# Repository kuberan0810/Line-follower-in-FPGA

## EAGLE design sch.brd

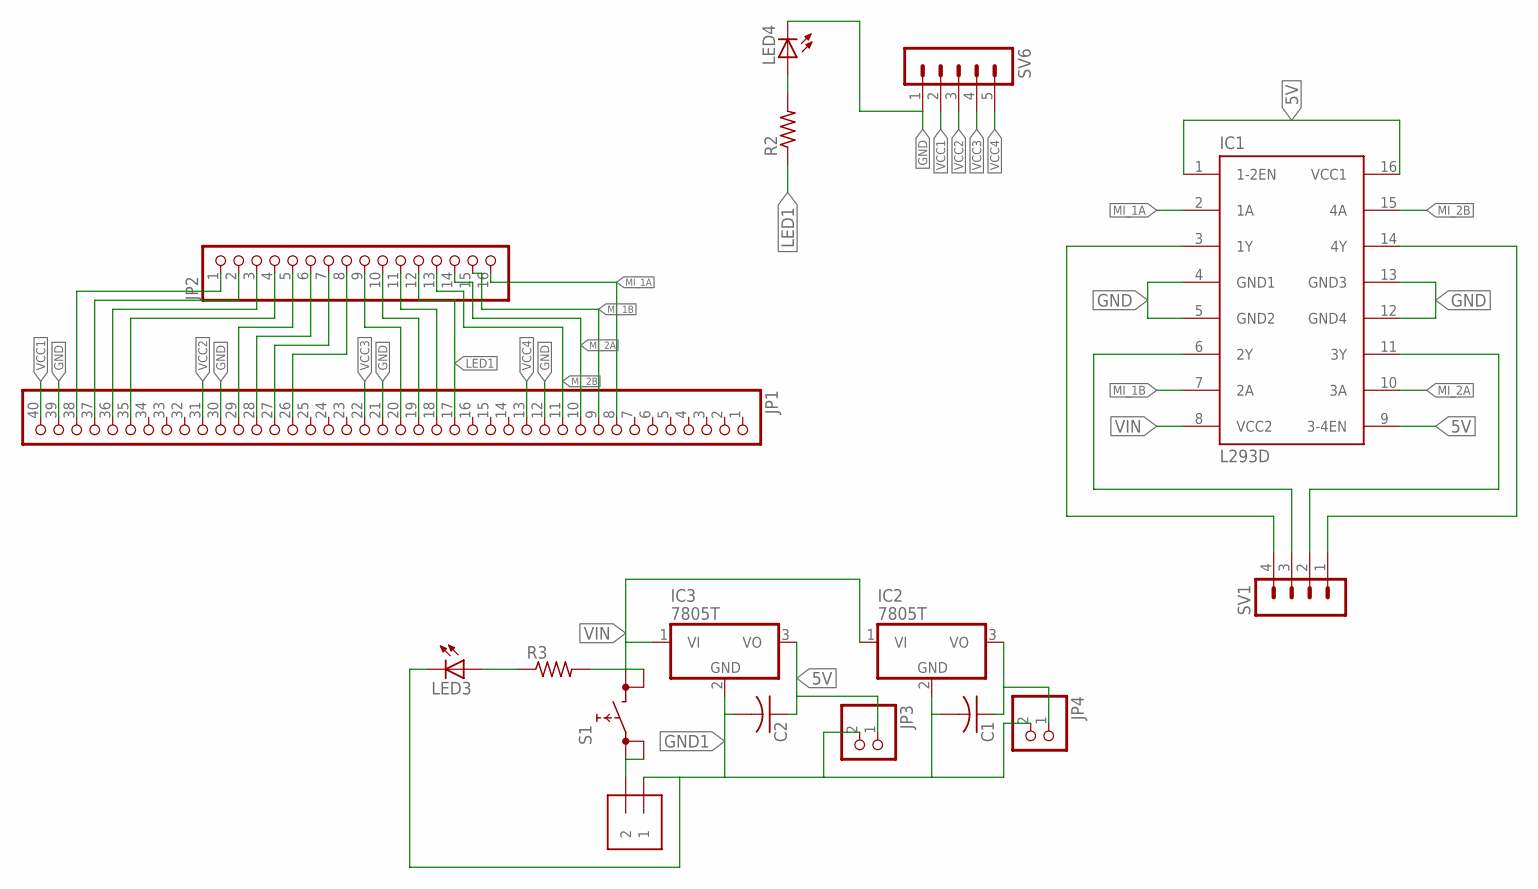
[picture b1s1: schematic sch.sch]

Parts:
C1, C2: C-US025-024X044; C025-024X044
IC1: L293D; DIL16
IC2, IC3: 7805T; TO220H
J1: 1X2-3.5MM
JP1: PINHD-1X40; 1X40
JP2: PINHD-1X16; 1X16
JP3, JP4: PINHD-1X2; 1X02
LED3, LED4: LED5MM
R2, R3: R-US_0204/2V; 0204V
S1: REKN
SV1: MA04-1
SV6: MA05-1

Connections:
5V: C2.1, IC1.1 (1-2EN), IC1.9 (3-4EN), IC1.16 (VCC1), IC3.3 (VO), JP3.1
GND: IC1.4 (GND1), IC1.5 (GND2), IC1.12 (GND4), IC1.13 (GND3), JP1.12, JP1.21, JP1.30, JP1.39, LED4.K (C), SV6.1
GND1: C1.2, C2.2, IC2.2 (GND), IC3.2 (GND), J1.1, JP3.2, JP4.2, LED3.K (C)
LED1: JP1.17, JP2.12, R2.1
MI_1A: IC1.2 (1A), JP1.8, JP2.16
MI_1B: IC1.7 (2A), JP1.9, JP2.15
MI_2A: IC1.10 (3A), JP1.10, JP2.14
MI_2B: IC1.15 (4A), JP1.11, JP2.13
unnamed: IC1.14 (4Y), SV1.1
unnamed: IC1.11 (3Y), SV1.2
unnamed: C1.1, IC2.3 (VO), JP4.1
unnamed: JP1.35, JP2.4
unnamed: JP1.27, JP2.7
unnamed: JP1.26, JP2.8
unnamed: LED4.A, R2.2
unnamed: JP1.38, JP2.1
unnamed: JP1.37, JP2.2
unnamed: JP1.36, JP2.3
unnamed: J1.2, S1.0A (0), S1.0B (0)
unnamed: JP1.29, JP2.5
unnamed: JP1.28, JP2.6
unnamed: LED3.A, R3.1
unnamed: IC1.6 (2Y), SV1.3
unnamed: JP1.20, JP2.9
unnamed: JP1.19, JP2.10
unnamed: JP1.18, JP2.11
unnamed: IC1.3 (1Y), SV1.4
VCC1: JP1.40, SV6.2
VCC2: JP1.31, SV6.3
VCC3: JP1.22, SV6.4
VCC4: JP1.13, SV6.5
VIN: IC1.8 (VCC2), IC2.1 (VI), IC3.1 (VI), R3.2, S1.1A (1), S1.1B (1)

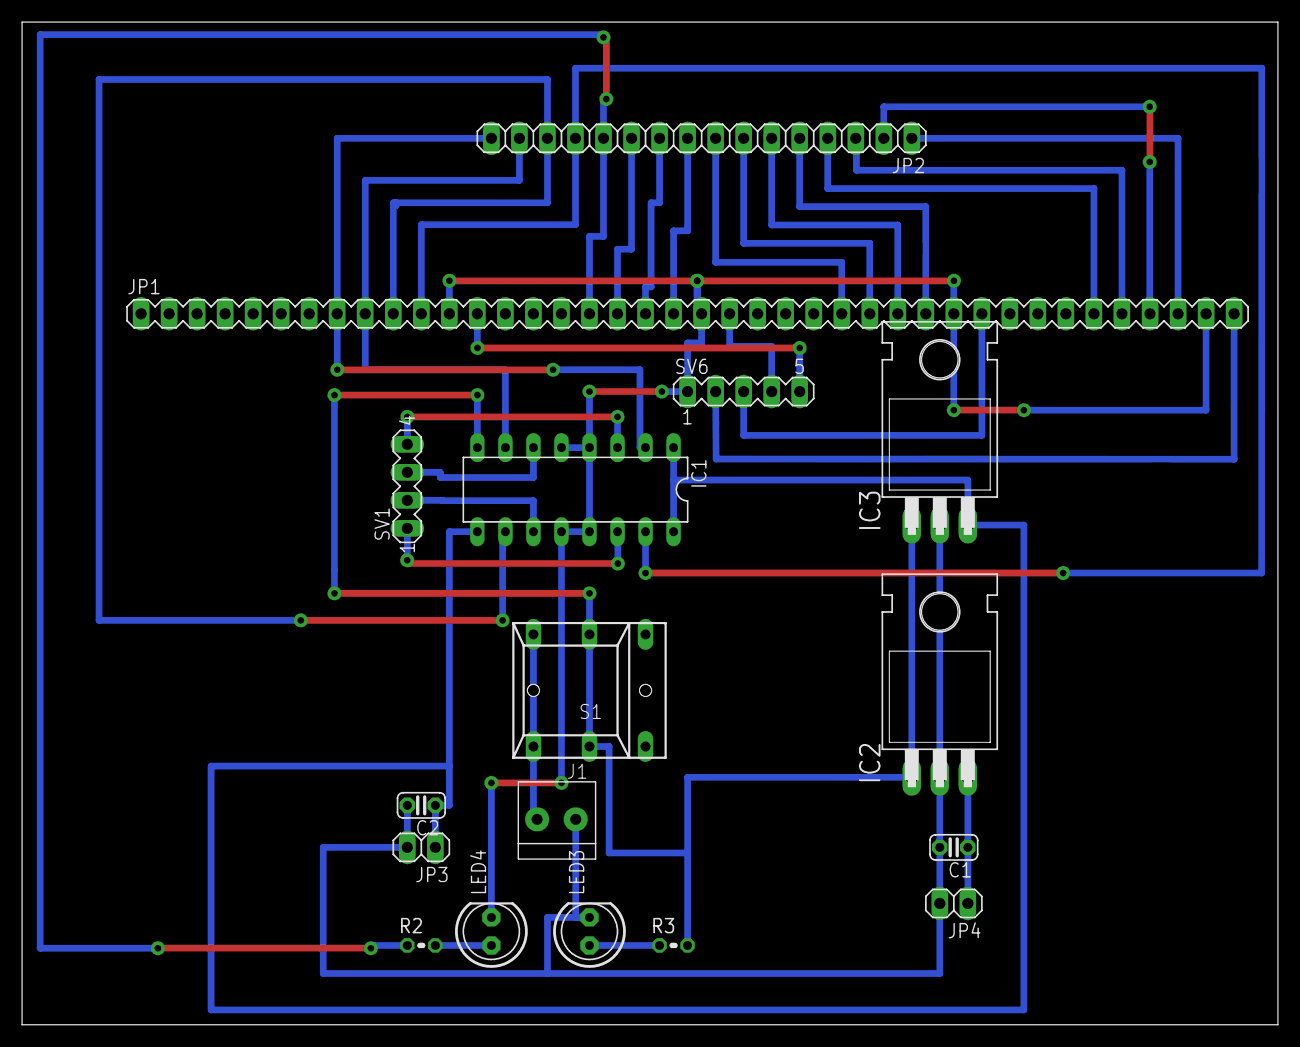
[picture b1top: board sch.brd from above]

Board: 2 copper layers, 113.8 x 90.9 mm, 17 parts (0 on the bottom side), 32 nets.

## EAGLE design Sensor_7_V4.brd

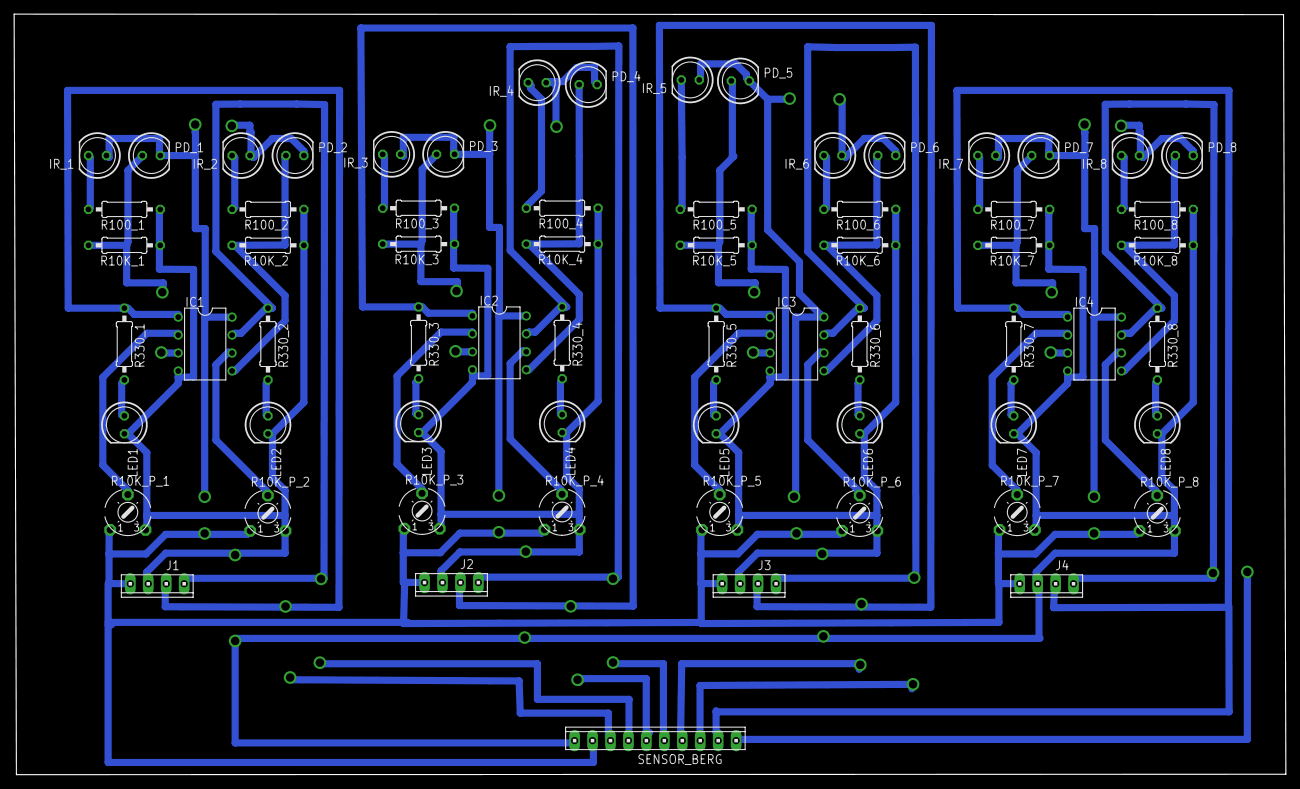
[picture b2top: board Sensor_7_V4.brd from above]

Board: 2 copper layers, 179.9 x 107.6 mm, 65 parts (0 on the bottom side), 48 nets.

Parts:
IC1, IC2, IC3, IC4: LM358N; DIL08
IR_1, IR_2, IR_3, IR_4, IR_5, IR_6, IR_7, IR_8: LED5MM
J1, J2, J3, J4: 10X04MTA
LED1, LED2, LED3, LED4, LED5, LED6, LED7, LED8: LED5MM
PD_1, PD_2, PD_3, PD_4, PD_5, PD_6, PD_7, PD_8: LED5MM
R10K_1, R10K_2, R10K_3, R10K_4, R10K_5, R10K_6, R10K_7, R10K_8, R100_1, R100_2, R100_3, R100_4, R100_5, R100_6, R100_7, R100_8, R330_1, R330_2, R330_3, R330_4, R330_5, R330_6, R330_7, R330_8: 0207/10
R10K_P_1, R10K_P_2, R10K_P_3, R10K_P_4, R10K_P_5, R10K_P_6, R10K_P_7, R10K_P_8: 6MM
SENSOR_BERG: 10X10MTA

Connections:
GND1: IC1.4, J1.2, LED1.K, LED2.K, R10K_1.1, R10K_2.1, R10K_P_1.E, R10K_P_2.E, R100_1.1, R100_2.1
GND2: IC2.4, J2.2, LED3.K, LED4.K, R10K_3.1, R10K_4.1, R10K_P_3.E, R10K_P_4.E, R100_3.1, R100_4.1
GND3: IC3.4, J3.2, LED5.K, LED6.K, R10K_5.1, R10K_6.1, R10K_P_5.E, R10K_P_6.E, R100_5.1, R100_6.1
GND4: IC4.4, J4.2, LED7.K, LED8.K, R10K_7.1, R10K_8.1, R10K_P_7.E, R10K_P_8.E, R100_7.1, R100_8.1
IC4_1: IC1.3, PD_1.A, R10K_1.2
IC4_2: IC1.5, PD_2.A, R10K_2.2
IC4_3: IC4.3, PD_7.A, R10K_7.2
IC4_4: IC2.3, PD_3.A, R10K_3.2
IC4_5: IC4.5, PD_8.A, R10K_8.2
IC4_6: IC2.5, PD_4.A, R10K_4.2
IC4_7: IC3.3, PD_5.A, R10K_5.2
IC4_8: IC3.5, PD_6.A, R10K_6.2
unnamed: LED1.A, R330_1.2
unnamed: LED2.A, R330_2.2
unnamed: IC1.6, R10K_P_2.S
unnamed: IR_1.K, R100_1.2
unnamed: IR_2.K, R100_2.2
unnamed: IC1.2, R10K_P_1.S
unnamed: LED3.A, R330_3.2
unnamed: LED4.A, R330_4.2
unnamed: IC2.6, R10K_P_4.S
unnamed: IR_3.K, R100_3.2
unnamed: IR_4.K, R100_4.2
unnamed: IC2.2, R10K_P_3.S
unnamed: LED7.A, R330_7.2
unnamed: LED8.A, R330_8.2
unnamed: IC4.6, R10K_P_8.S
unnamed: IR_7.K, R100_7.2
unnamed: IR_8.K, R100_8.2
unnamed: IC4.2, R10K_P_7.S
unnamed: LED5.A, R330_5.2
unnamed: LED6.A, R330_6.2
unnamed: IC3.6, R10K_P_6.S
unnamed: IR_5.K, R100_5.2
unnamed: IR_6.K, R100_6.2
unnamed: IC3.2, R10K_P_5.S
SENSOR_1: IC1.1, J1.3, R330_1.1
SENSOR_2: IC1.7, J1.4, R330_2.1
SENSOR_3: IC2.1, J2.3, R330_3.1
SENSOR_4: IC2.7, J2.4, R330_4.1
SENSOR_5: IC3.1, J3.3, R330_5.1
SENSOR_6: IC3.7, J3.4, R330_6.1
SENSOR_7: IC4.1, J4.3, R330_7.1
SENSOR_8: IC4.7, J4.4, R330_8.1
VCC1: IC1.8, IR_1.A, IR_2.A, J1.1, PD_1.K, PD_2.K, R10K_P_1.A, R10K_P_2.A
VCC2: IC2.8, IR_3.A, IR_4.A, J2.1, PD_3.K, PD_4.K, R10K_P_3.A, R10K_P_4.A
VCC3: IC3.8, IR_5.A, IR_6.A, J3.1, PD_5.K, PD_6.K, R10K_P_5.A, R10K_P_6.A
VCC4: IC4.8, IR_7.A, IR_8.A, J4.1, PD_7.K, PD_8.K, R10K_P_7.A, R10K_P_8.A
